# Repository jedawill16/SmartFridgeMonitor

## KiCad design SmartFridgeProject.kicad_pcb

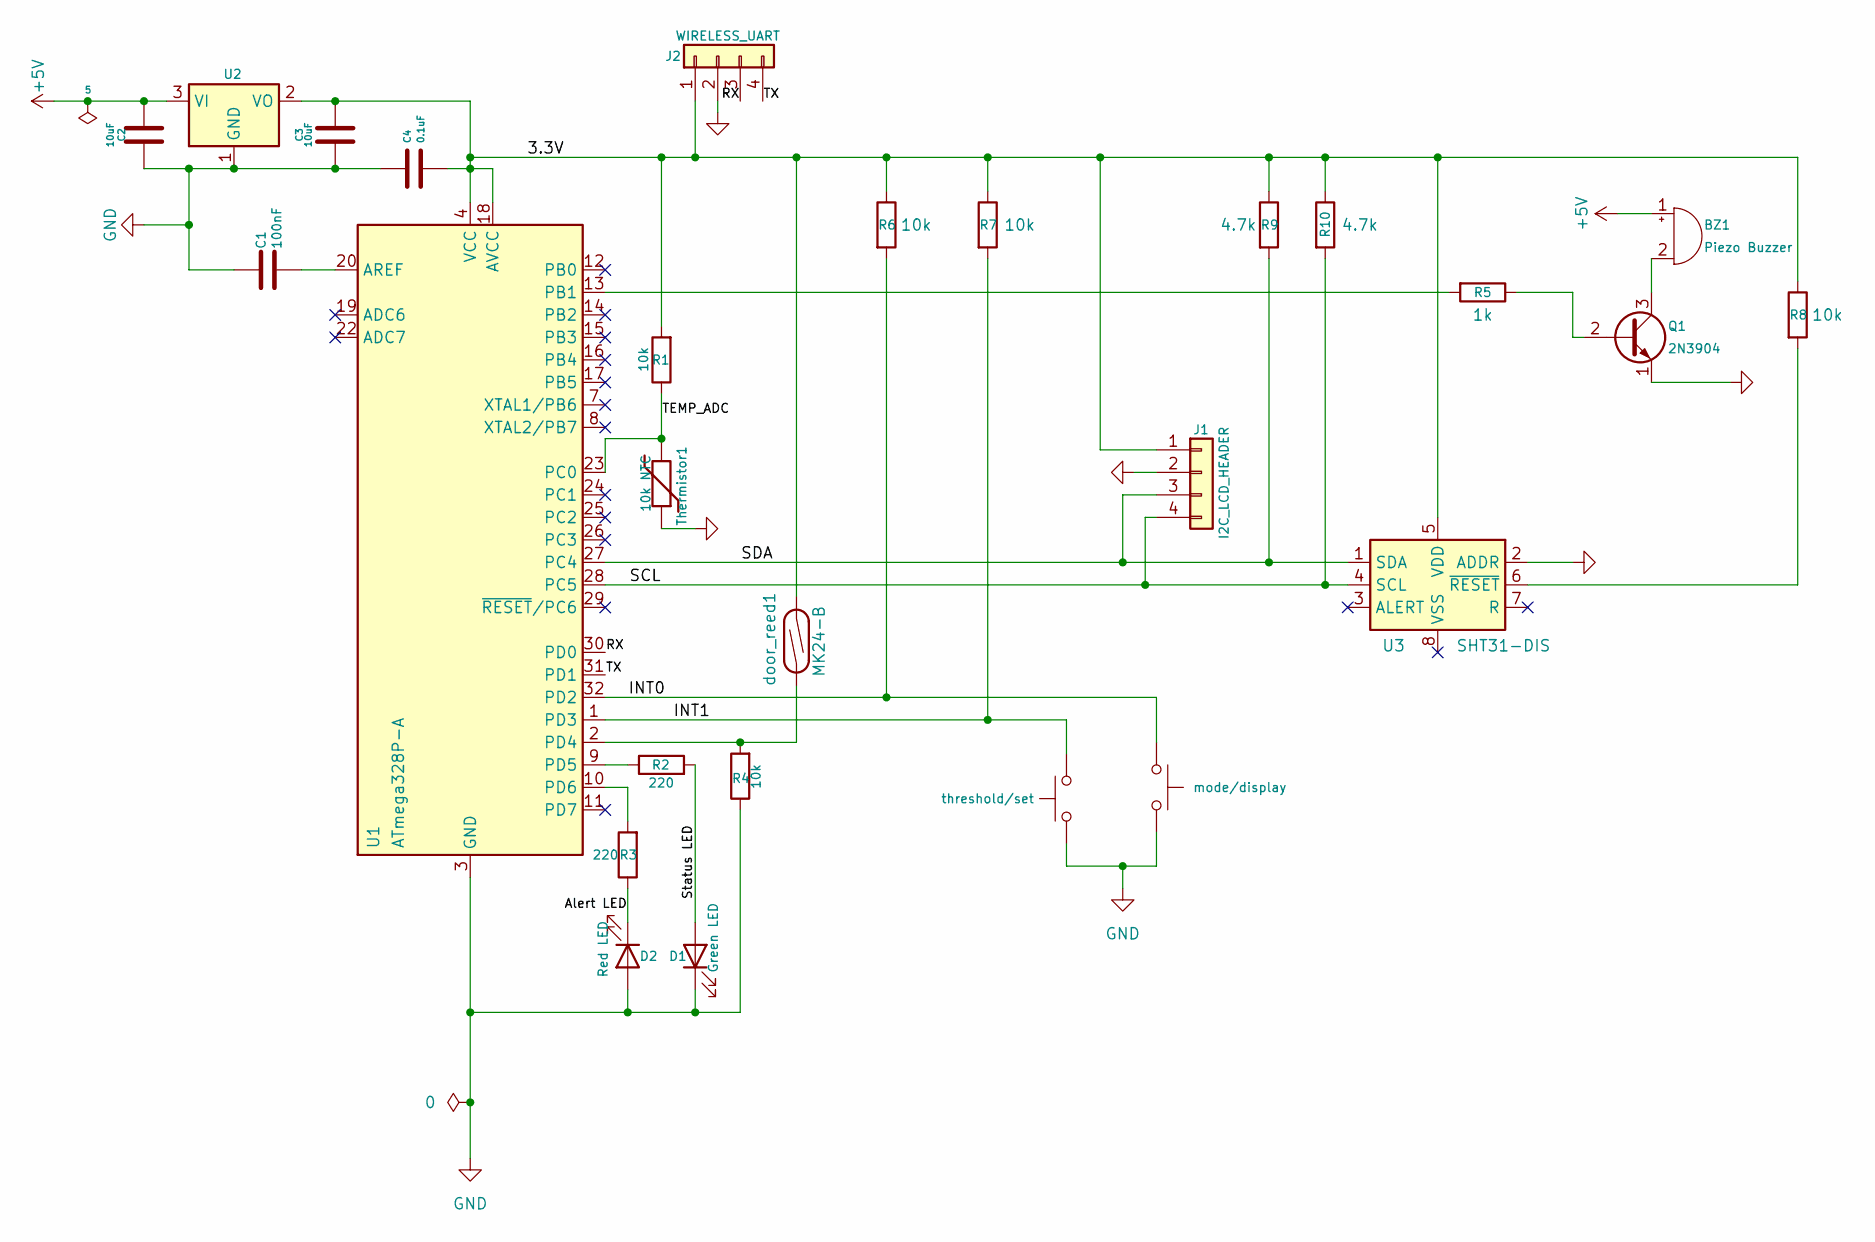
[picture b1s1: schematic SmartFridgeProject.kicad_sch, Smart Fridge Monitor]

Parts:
BZ1: Piezo Buzzer; Buzzer_12x9.5RM7.6
C1: 100nF; C_Disc_D5.0mm_W2.5mm_P2.50mm
C2, C3: 10uF; CP_Radial_D5.0mm_P2.00mm
C4: 0.1uF; C_Disc_D5.0mm_W2.5mm_P2.50mm
D1: Green LED; LED_D5.0mm
D2: Red LED; LED_D5.0mm
J1: I2C_LCD_HEADER; PinHeader_1x04_P2.54mm_Vertical
J2: WIRELESS_UART; PinHeader_1x04_P2.54mm_Vertical
Q1: 2N3904; TO-92_Inline
R1, R4, R6, R7, R8: 10k; R_Axial_DIN0207_L6.3mm_D2.5mm_P7.62mm_Horizontal
R2, R3: 220; R_Axial_DIN0207_L6.3mm_D2.5mm_P7.62mm_Horizontal
R5: 1k; R_Axial_DIN0207_L6.3mm_D2.5mm_P7.62mm_Horizontal
R9, R10: 4.7k; R_Axial_DIN0207_L6.3mm_D2.5mm_P7.62mm_Horizontal
SW2: threshold/set; SW_PUSH_6mm
SW3: mode/display; SW_PUSH_6mm
Thermistor1: 10k NTC; R_Axial_DIN0207_L6.3mm_D2.5mm_P7.62mm_Horizontal
U1: ATmega328P-A; TQFP-32_7x7mm_P0.8mm
U2: AMS1117-3.3; SOT-223-3_TabPin2
U3: SHT31-DIS; Sensirion_DFN-8-1EP_2.5x2.5mm_P0.5mm_EP1.1x1.7mm
door_reed1: MK24-B; PinHeader_1x02_P2.54mm_Vertical

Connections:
+5V: BZ1.1 (+), C2.2, U2.3 (VI)
/3.3V: C3.2, C4.2, J1.1, J2.1, R1.2, R6.1, R7.1, R8.1, R9.1, R10.1, U1.4 (VCC), U1.6 (VCC), U1.18 (AVCC), U2.2 (VO), U3.5 (VDD), door_reed1.2
/Alert LED: D2.1 (K), R3.1
/INT0: R6.2, SW3.1, U1.32 (PD2)
/INT1: R7.2, SW2.2, U1.1 (PD3)
/RX: J2.3, U1.30 (PD0)
/SCL: J1.4, R10.2, U1.28 (PC5), U3.4 (SCL)
/SDA: J1.3, R9.2, U1.27 (PC4), U3.1 (SDA)
/Status LED: D1.2 (A), R2.2
/TEMP_ADC: R1.1, Thermistor1.2, U1.23 (PC0)
/TX: J2.4, U1.31 (PD1)
GND: C1.1, C2.1, C3.1, C4.1, D1.1 (K), D2.2 (A), J1.2, J2.2, Q1.1 (E), R4.1, SW2.1, SW3.2, Thermistor1.1, U1.3 (GND), U1.5 (GND), U1.21 (GND), U2.1 (GND), U3.2 (ADDR)
unnamed: BZ1.2 (-), Q1.3 (C)
unnamed: Q1.2 (B), R5.1
unnamed: C1.2, U1.20 (AREF)
unnamed: R5.2, U1.13 (PB1)
unnamed: R4.2, U1.2 (PD4), door_reed1.1
unnamed: R2.1, U1.9 (PD5)
unnamed: R3.2, U1.10 (PD6)
unnamed: R8.2, U3.6 (~RESET)

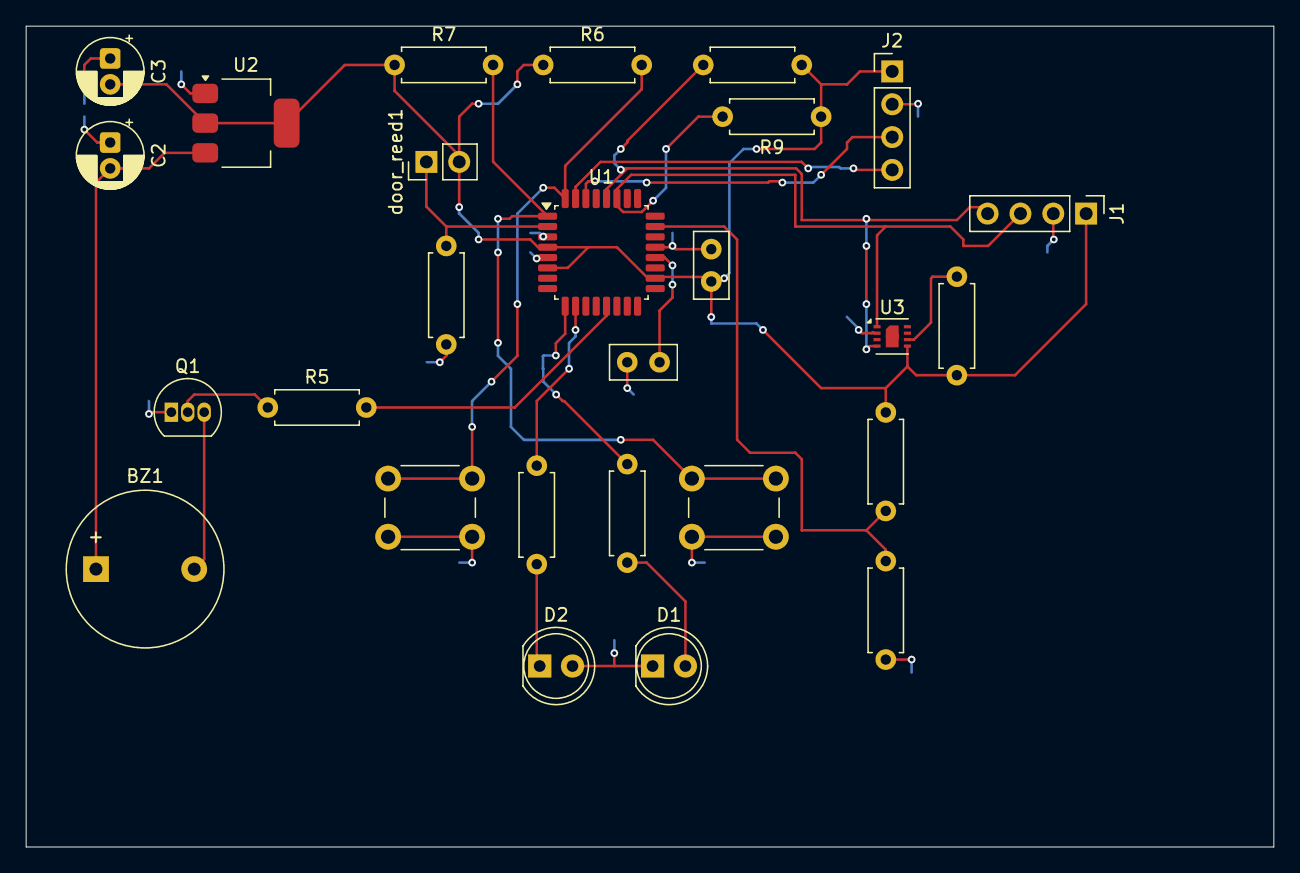
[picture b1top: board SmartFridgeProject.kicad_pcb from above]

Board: 2 copper layers, 96.5 x 63.5 mm, 27 parts (0 on the bottom side), 20 nets.

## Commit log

2026-04-28 initial commit; contains .sch and .pcb
2026-04-28 pcb trace finished; other misc. changes
2026-04-28 added gerber files for final report
